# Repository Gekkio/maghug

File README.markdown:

# maghug

A battery-powered device that blinks a LED if it doesn't get hugs from a magnet.

## What?

If the magnet **(B)** near the sensor **(A)** is removed for a long period of
time, the microcontroller **(D)** powered by the CR2032 coin cell battery
**(C)** starts blinking the red LED **(E)**.

In this example the magnet is actually an old broken speaker, but any magnet of
sufficient strength will do.

## Bill Of Materials (BOM)

| Part  | Description                             | Mouser link                                                                                                |
| ----: | --------------------------------------- | ---------------------------------------------------------------------------------------------------------- |
| U1    | microcontroller, SOT-23 package         | [Microchip PIC10LF322T-E/OT](http://www.mouser.com/search/ProductDetail.aspx?r=579%2dPIC10LF322T%2dE%2fOT) |
| U2    | boost regulator, SOT-23 package         | [Microchip MCP16252T-I/CH](http://www.mouser.com/search/ProductDetail.aspx?r=579%2dMCP16252T%2dI%2fCH)     |
| U3    | hall effect sensor, SC59 package        | [Diodes Inc. AH1802-WG-7](http://www.mouser.com/search/ProductDetail.aspx?r=621%2dAH1802%2dWG%2d7)         |
| L1    | 4.7 µH inductor, surface mount          | [TDK VLS3015ET-4R7M](http://www.mouser.com/search/ProductDetail.aspx?r=810%2dVLS3015ET%2d4R7M)             |
| R1    | 10 KΩ resistor, 0603 package            |                                                                                                            |
| R2    | 1.69 MΩ resistor, 0603 package          |                                                                                                            |
| R3    | 1 MΩ resistor, 0603 package             |                                                                                                            |
| R4    | 1 MΩ resistor, 0603 package             |                                                                                                            |
| R5    | 2.2 KΩ resistor, 0603 package           |                                                                                                            |
| R6    | 1 KΩ resistor, 0603 package             |                                                                                                            |
| C1    | 4.7 µF ceramic capacitor, 0805 package  |                                                                                                            |
| C2    | 0.1 µF ceramic capacitor, 0603 package  |                                                                                                            |
| C3    | 10 µF ceramic capacitor, 0805 package   |                                                                                                            |
| D1    | Red LED, through-hole                   |                                                                                                            |
| D2    | Green LED, through-hole                 |                                                                                                            |
| BAT1  | CR2032 battery holder, surface mount    | [Linx BAT-HLD-001](http://www.mouser.com/search/ProductDetail.aspx?r=712%2dBAT%2dHLD%2d001)                |
| J1    | 0.1" header, 5 pins, through-hole       |                                                                                                            |

## License and copyright

### Hardware

Copyright 2016 Joonas Javanainen joonas.javanainen@gmail.com

The maghug hardware is licensed under a
[Creative Commons Attribution 4.0 International License](http://creativecommons.org/licenses/by/4.0/).

Eagle libraries used:

* [Gekkio Eagle Libraries](https://github.com/Gekkio/gekkio-eagle-libraries)
* [SparkFun Electronics Eagle Libraries](https://github.com/sparkfun/SparkFun-Eagle-Libraries)

### Software

Copyright 2016 Joonas Javanainen joonas.javanainen@gmail.com

Licensed under the Apache License, Version 2.0 (the "License");
you may not use this file except in compliance with the License.
You may obtain a copy of the License at

http://www.apache.org/licenses/LICENSE-2.0

Unless required by applicable law or agreed to in writing, software
distributed under the License is distributed on an "AS IS" BASIS,
WITHOUT WARRANTIES OR CONDITIONS OF ANY KIND, either express or implied.
See the License for the specific language governing permissions and
limitations under the License.

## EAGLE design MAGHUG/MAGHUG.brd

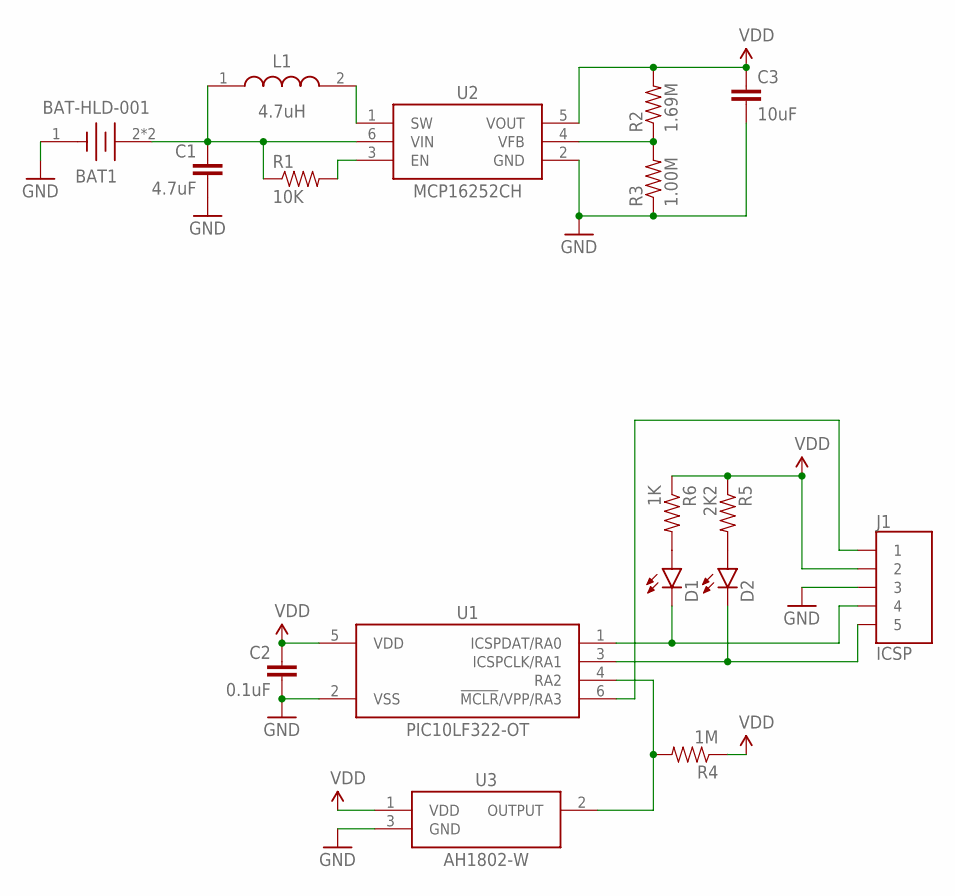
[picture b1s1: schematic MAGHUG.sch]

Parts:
BAT1: BAT-HLD-001
C1: 4.7uF; 0805
C2: 0.1uF; 0603-CAP
C3: 10uF; 0805
D1, D2: LED-3MM-NO_SILK; LED3MM-NS
J1: ICSP; 1X5-LONGPADS
L1: 4.7uH; VLS3015E
R1: 10K; 0603-RES
R2: 1.69M; 0603-RES
R3: 1.00M; 0603-RES
R4: 1M; 0603-RES
R5: 2K2; 0603-RES
R6: 1K; 0603-RES
U1: PIC10LF322-OT; SOT-23(CH/CHY/OT)
U2: MCP16252CH; SOT-23(CH/CHY/OT)
U3: AH1802-W; SC59

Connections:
!MCLR: J1.1, U1.6 (!MCLR!/VPP/RA3)
EN: R1.2, U2.3 (EN)
GND: BAT1.1 (-), C1.2, C2.2, C3.2, J1.3, R3.1, U1.2 (VSS), U2.2 (GND), U3.3 (GND)
unnamed: R4.2, U1.4 (RA2), U3.2 (OUTPUT)
unnamed: D1.A, R6.2
unnamed: D2.A, R5.2
RA0: D1.K (C), J1.4, U1.1 (ICSPDAT/RA0)
RA1: D2.K (C), J1.5, U1.3 (ICSPCLK/RA1)
SW: L1.2, U2.1 (SW)
VBAT: BAT1.2 (+), BAT1.3 (+), C1.1, L1.1, R1.1, U2.6 (VIN)
VDD: C2.1, C3.1, J1.2, R2.2, R4.1, R5.1, R6.1, U1.5 (VDD), U2.5 (VOUT), U3.1 (VDD)
VFB: R2.1, R3.2, U2.4 (VFB)

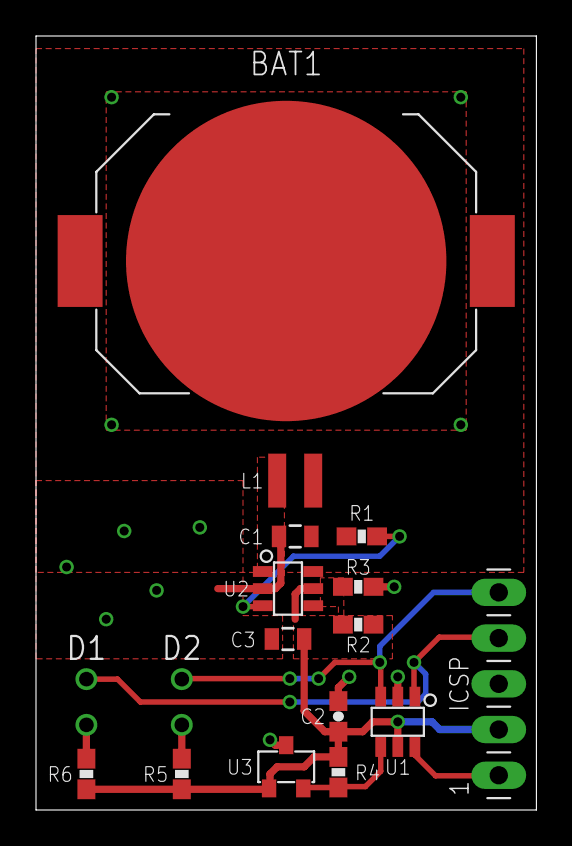
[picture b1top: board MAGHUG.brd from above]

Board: 2 copper layers, 27.8 x 43.0 mm, 17 parts (0 on the bottom side), 12 nets.

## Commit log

2016-09-24 Add a photo of v1.0 board
2016-09-24 Add a short explanation of what the device does

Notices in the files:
parts and their libraries:
SparkFun-Passives: Licensing: Creative Commons ShareAlike 4.0 International - https://creativecommons.org/licenses/by-sa/4.0
